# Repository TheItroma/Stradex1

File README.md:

STRADEX1
==============
An electronic instrument crossover between a violin, a mandolin and an otamatone

I've always wanted to put my violin skills to use in a MIDI environment, but there really isn't a controller on the market that can emulate the feel of a violin to the extent that Stradex does. 

Stradex features a SoftPot linear resistor to emulate the violin/mandolin fingerboard, four custom force-sensitive keys to emulate the strings, and three potentiometers for range & modulation control. This setup allows Stradex to generate pitch bends, vibrato, dynamic expression, and incredible range, all while remaining intuitive for the average string player. 

This project took me a good while. Sure, there was a lot of time spent fiddling with faulty ADS1115 chips and iterating on key designs, but most of the headscratching was in the embedded firmware, namely, the MIDI signal interface. Many digital signal filtering and processing techniques had to be employed, including buffering, low-pass filtering, digital hysterisis, and numerous serial optimizations to ensure the controller intellegently decided when to send MIDI signals and when to ignore them. 

## Build guide : 

### [**Over here !**](Docs/BuildGuide.md)

If you already have quite a bit of experience or
just don't want the bloat of the beginner guide : [This is the advanced guide](Docs/AdvancedBuildGuide.md)

Check out my website for more projects + contact me.

[My Website](https://bradylin.com/)

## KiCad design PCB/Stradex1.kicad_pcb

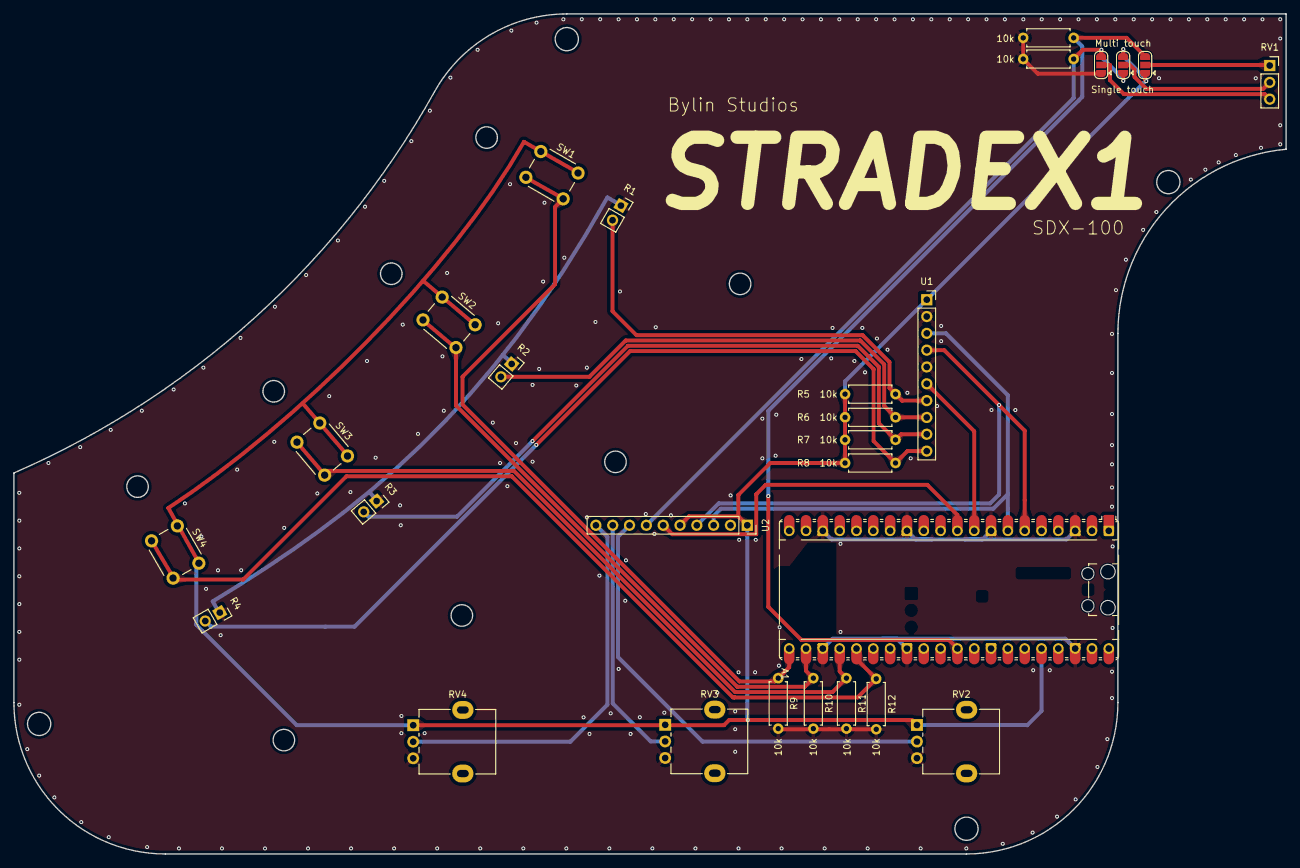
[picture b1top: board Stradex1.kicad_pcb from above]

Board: 2 copper layers, 192.1 x 126.9 mm, 28 parts (0 on the bottom side), 22 nets.

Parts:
A1: RaspberryPi_Pico; RaspberryPi_Pico_Common_Unspecified
R1, R2, R3, R4: FSR; PinSocket_1x02_P2.54mm_Vertical
R5, R6, R7, R8, R9, R10, R11, R12, R13, R17: 10k; R_Axial_DIN0207_L6.3mm_D2.5mm_P7.62mm_Horizontal
RV1: SoftPot; PinSocket_1x03_P2.54mm_Vertical
RV2, RV3, RV4: R_Pot; Potentiometer_Alpha_RD901F-40-00D_Single_Vertical
SW1, SW2, SW3, SW4: SW_Push; SW_PUSH_6mm
SW5, SW6, SW7: MT_JUMPER_1; SolderJumper-3_P1.3mm_Open_RoundedPad1.0x1.5mm
U1, U2: ADS1115IDGS; PinSocket_1x10_P2.54mm_Vertical

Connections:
+3.3V: A1.36 (3V3), R5.2, R6.2, R7.2, R8.2, RV2.1, RV3.1, RV4.1, SW1.1, SW2.1, SW3.1, SW4.1, SW5.3 (C), SW7.1 (A), U1.1 (VDD), U2.1 (VDD), U2.5 (ADDR)
/ALRT1: A1.9 (GPIO6), U1.6 (ALERT/RDY)
/ALRT2: A1.10 (GPIO7), U2.6 (ALERT/RDY)
/FSR1: R1.2, R5.1, U1.7 (AIN0)
/FSR2: R2.2, R6.1, U1.8 (AIN1)
/FSR3: R3.2, R7.1, U1.9 (AIN2)
/FSR4: R4.2, R8.1, U1.10 (AIN3)
/P1: RV2.2, U2.8 (AIN1)
/P2: RV3.2, U2.9 (AIN2)
/P3: RV4.2, U2.10 (AIN3)
/PB1: A1.21 (GPIO16), R9.1, SW1.2
/PB2: A1.22 (GPIO17), R10.1, SW2.2
/PB3: A1.24 (GPIO18), R11.1, SW3.2
/PB4: A1.25 (GPIO19), R12.1, SW4.2
/SCL: A1.7 (GPIO5), U1.3 (SCL), U2.3 (SCL)
/SDA: A1.6 (GPIO4), U1.4 (SDA), U2.4 (SDA)
/SPot: R17.2, SW5.1 (A), SW6.3 (C), U2.7 (AIN0)
/SPot_MT: A1.31 (GPIO26_ADC0), R13.1, SW7.3 (C)
GND: A1.3 (GND), A1.8 (GND), A1.13 (GND), A1.18 (GND), A1.23 (GND), A1.28 (GND), A1.38 (GND), R1.1, R2.1, R3.1, R4.1, R9.2, R10.2, R11.2, R12.2, R13.2, R17.1, RV2.3, RV3.3, RV4.3, SW6.1 (A), U1.2 (GND), U1.5 (ADDR), U2.2 (GND)
unnamed: RV1.2, SW5.2 (B)
unnamed: RV1.3, SW6.2 (B)
unnamed: RV1.1, SW7.2 (B)

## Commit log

2025-08-31 Change Struct
2025-08-31 updated midi
2025-09-01 updated file structure
2025-09-10 Added new code
2025-09-10 MIDI MVP
2025-09-11 added fsr
2025-09-11 MVP for pitchbend
2025-09-11 deleted unessesary stuff
2025-09-11 readme
2025-09-11 Create LISCENSE
2025-09-11 added readme
2025-09-11 added files
2025-09-15 updated site
2025-09-25 modified a few things
2025-09-25 fixed ordering guide name
2025-09-25 Am I really that unfunny that I steal jokes from other people?
2025-09-25 Im not even belge
2025-09-25 another
2025-09-25 jesus im doing way to many commits lol
2025-09-25 another one
2025-09-25 and another one
2025-09-25 'Looks at the time' : 2h dissapeared
2025-09-25 added whatever
2025-09-25 fixed 1 link
2025-09-25 Folder Renames
2025-09-25 actual rename
2025-09-28 Made the pcb 2 layers and added a gnd copper fill
2025-10-09 Stole the pcb from 'Whitebowfr'
2025-10-14 fixed bom table for fsr
2026-02-02 Im working on this again
2026-02-02 removed duplicate file
